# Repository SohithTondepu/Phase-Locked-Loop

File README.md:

# PLL1 PCB Project

This repository contains the complete design and implementation of a basic Phase-Locked Loop (PLL) circuit, referred to as PLL1. The project was developed using KiCad for schematic capture and PCB layout, and includes all the necessary files for fabrication and assembly.
Before finalizing the PCB, the circuit was first tested on a perfboard to verify its functionality. Once validated, the PCB was fabricated and components were soldered manually.

# Preview
Assembled PCB

Prototype Testing on Perfboard

# Project Structure
```
PLL1-PCB-Project/
├── src/
│   ├── PLL1.sch                  # Schematic file
│   ├── PLL1.kicad_pcb            # PCB layout
│   ├── PLL1.pro                  # KiCad project file
│   └── custom footprints/        # Custom footprint libraries
│
├── output/
│   ├── BOM.csv                   # Bill of Materials
│   ├── PickAndPlace.csv          # Component placement data
│   ├── pll1.drl                  # Drill file
│   ├── *.gbr                     # Gerber fabrication files
│
├── media/
│   ├── pll1-real-board.jpg       # Final PCB image
│   └── pll1-proto-board.jpg      # Perfboard prototype image
│
└── README.md                     # Project documentation
```

## Tools Used

* KiCad 8.0 – for creating the schematic and PCB layout
* Manual soldering – to assemble the fabricated PCB
* Perfboard – used for initial testing and verification of the circuit

## Output Files

The `output/` directory contains all necessary files for PCB fabrication and assembly:

* Gerber files
* Drill file
* Bill of Materials (BOM)
* Pick-and-place file

## Applications

This project is intended for educational purposes and hands-on practice. It’s a simple yet effective way to understand the working of PLL circuits and gain experience in:

* Schematic and PCB design
* Manual soldering techniques
* PCB fabrication process

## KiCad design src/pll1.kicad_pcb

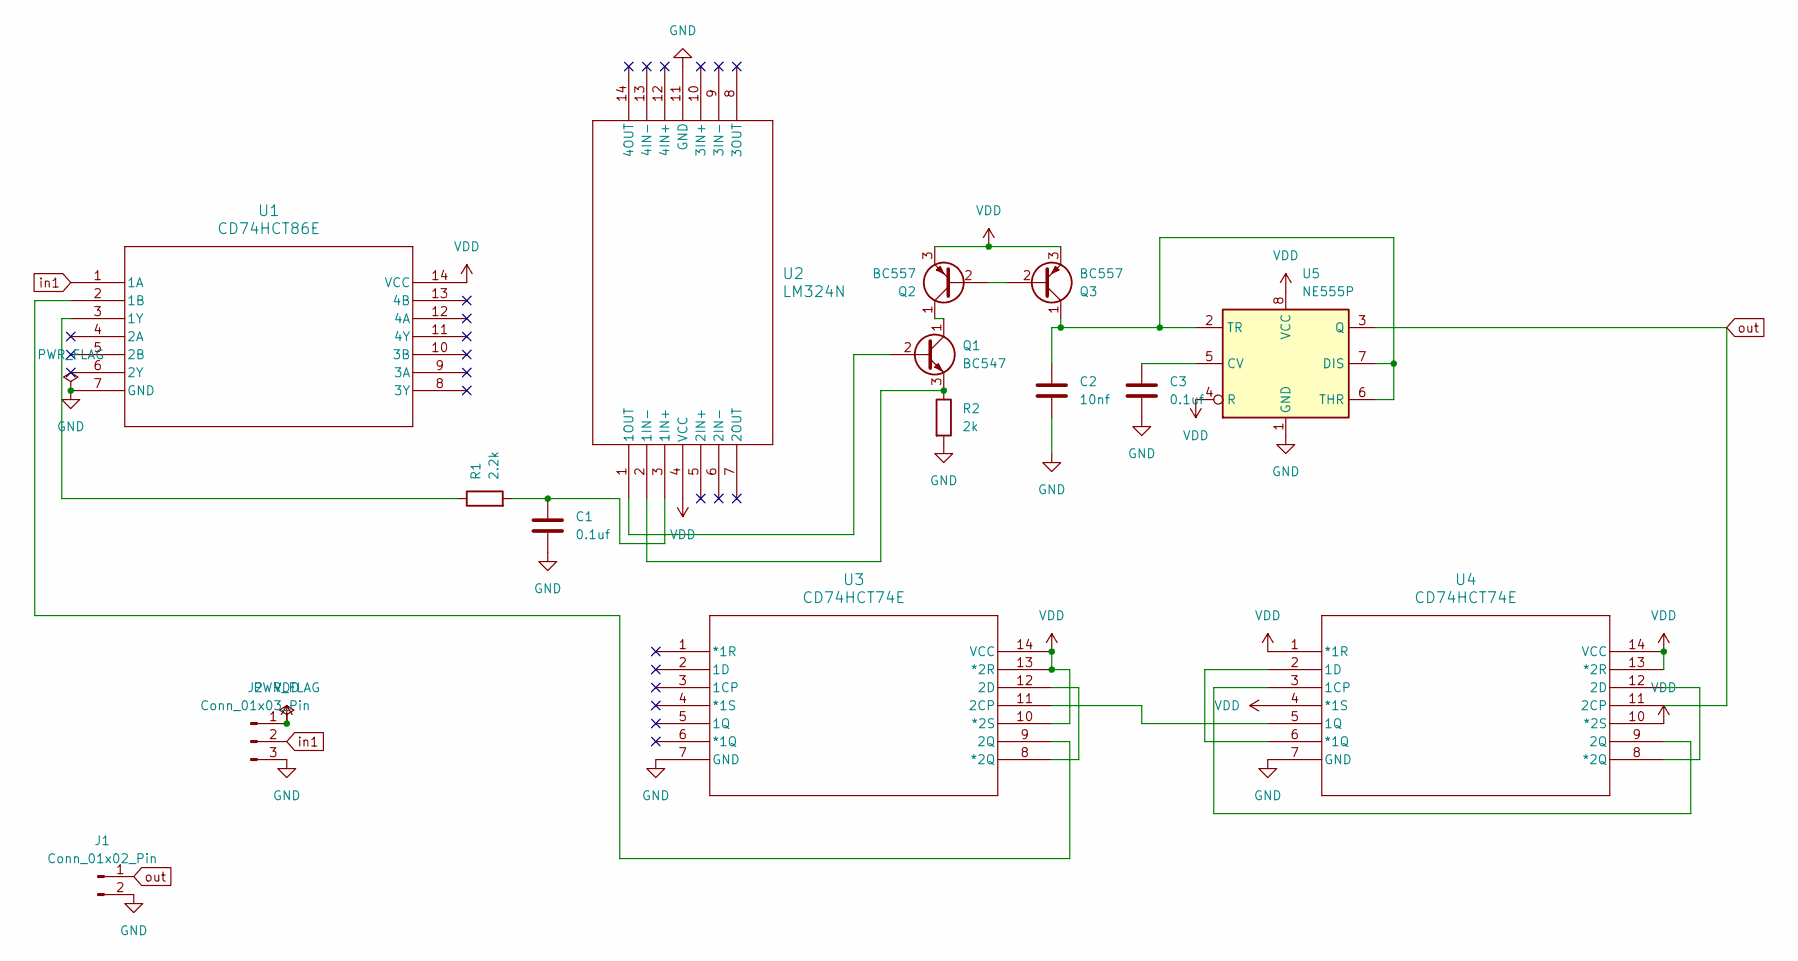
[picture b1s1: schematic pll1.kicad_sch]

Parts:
C1: 0.1uf; CP_Radial_D8.0mm_P3.80mm
C2: 10nf; CP_Radial_D8.0mm_P5.00mm
C3: 0.1uf; CP_Radial_D8.0mm_P3.50mm
J1: Conn_01x02_Pin; PinHeader_1x02_P2.00mm_Vertical
J2: Conn_01x03_Pin; PinHeader_1x03_P2.00mm_Vertical
Q1: BC547; TO-92_Inline
Q2, Q3: BC557; TO-92_Inline
R1: 2.2k; R_Axial_DIN0207_L6.3mm_D2.5mm_P10.16mm_Horizontal
R2: 2k; R_Axial_DIN0207_L6.3mm_D2.5mm_P7.62mm_Horizontal
U1: CD74HCT86E; N14
U2: LM324N; N14
U3, U4: CD74HCT74E; N14
U5: NE555P; DIP-8_W7.62mm

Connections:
GND: C1.2, C2.2, C3.2, J1.2, J2.3, R2.2, U1.7 (GND), U2.11 (GND), U3.7 (GND), U4.7 (GND), U5.1 (GND)
unnamed: Q1.2 (B), U2.1 (1OUT)
unnamed: Q1.1 (C), Q2.1 (C)
unnamed: Q1.3 (E), R2.1, U2.2 (1IN-)
unnamed: Q2.2 (B), Q3.2 (B)
unnamed: C2.1, Q3.1 (C), U5.2 (TR), U5.6 (THR), U5.7 (DIS)
unnamed: U1.2 (1B), U3.9 (2Q)
unnamed: R1.1, U1.3 (1Y)
unnamed: C1.1, R1.2, U2.3 (1IN+)
unnamed: U3.11 (2CP), U4.5 (1Q)
unnamed: U3.8 (*2Q), U3.12 (2D)
unnamed: U4.3 (1CP), U4.9 (2Q)
unnamed: U4.2 (1D), U4.6 (*1Q)
unnamed: U4.8 (*2Q), U4.12 (2D)
unnamed: C3.1, U5.5 (CV)
VDD: J2.1, Q2.3 (E), Q3.3 (E), U1.14 (VCC), U2.4 (VCC), U3.10 (*2S), U3.13 (*2R), U3.14 (VCC), U4.1 (*1R), U4.4 (*1S), U4.10 (*2S), U4.13 (*2R), U4.14 (VCC), U5.4 (R), U5.8 (VCC)
in1: J2.2, U1.1 (1A)
out: J1.1, U4.11 (2CP), U5.3 (Q)

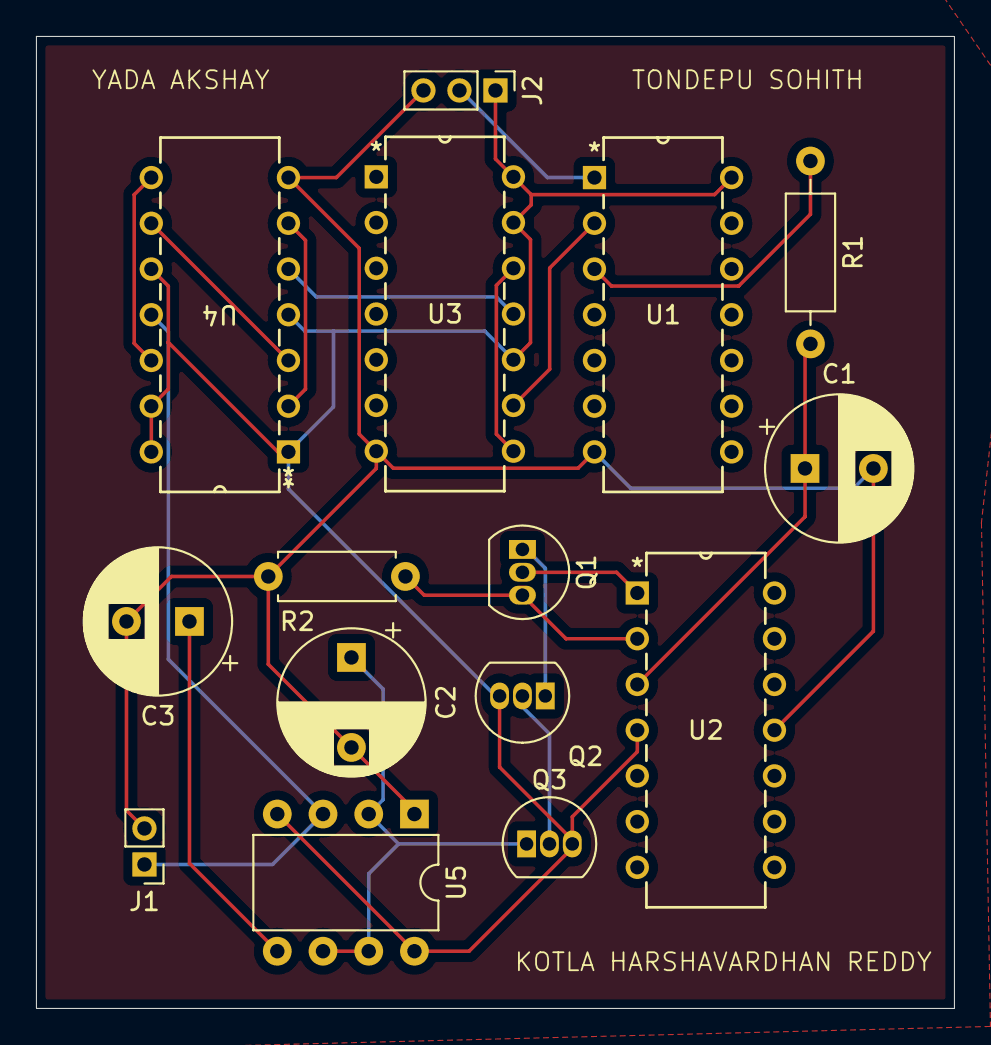
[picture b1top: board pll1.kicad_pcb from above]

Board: 2 copper layers, 51.0 x 54.0 mm, 15 parts (0 on the bottom side), 18 nets.

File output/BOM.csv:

"Reference","Value","Datasheet","Footprint","Qty","DNP"
"C1,C3","0.1uf","~","-- mixed values --","2",""
"C2","10nf","~","Capacitor_THT:CP_Radial_D8.0mm_P5.00mm","1",""
"J1","Conn_01x02_Pin","~","Connector_PinHeader_2.00mm:PinHeader_1x02_P2.00mm_Vertical","1",""
"J2","Conn_01x03_Pin","~","Connector_PinHeader_2.00mm:PinHeader_1x03_P2.00mm_Vertical","1",""
"Q1","BC547","https://www.onsemi.com/pub/Collateral/BC550-D.pdf","Package_TO_SOT_THT:TO-92_Inline","1",""
"Q2,Q3","BC557","https://www.onsemi.com/pub/Collateral/BC556BTA-D.pdf","Package_TO_SOT_THT:TO-92_Inline","2",""
"R1","2.2k","~","Resistor_THT:R_Axial_DIN0207_L6.3mm_D2.5mm_P10.16mm_Horizontal","1",""
"R2","2k","~","Resistor_THT:R_Axial_DIN0207_L6.3mm_D2.5mm_P7.62mm_Horizontal","1",""
"U1","CD74HCT86E","CD74HCT86E","xorfoot:N14","1",""
"U2","LM324N","LM324N","lm324foot:N14","1",""
"U3,U4","CD74HCT74E","CD74HCT74E","pll flip:N14","2",""
"U5","NE555P","http://www.ti.com/lit/ds/symlink/ne555.pdf","Package_DIP:DIP-8_W7.62mm","1",""
